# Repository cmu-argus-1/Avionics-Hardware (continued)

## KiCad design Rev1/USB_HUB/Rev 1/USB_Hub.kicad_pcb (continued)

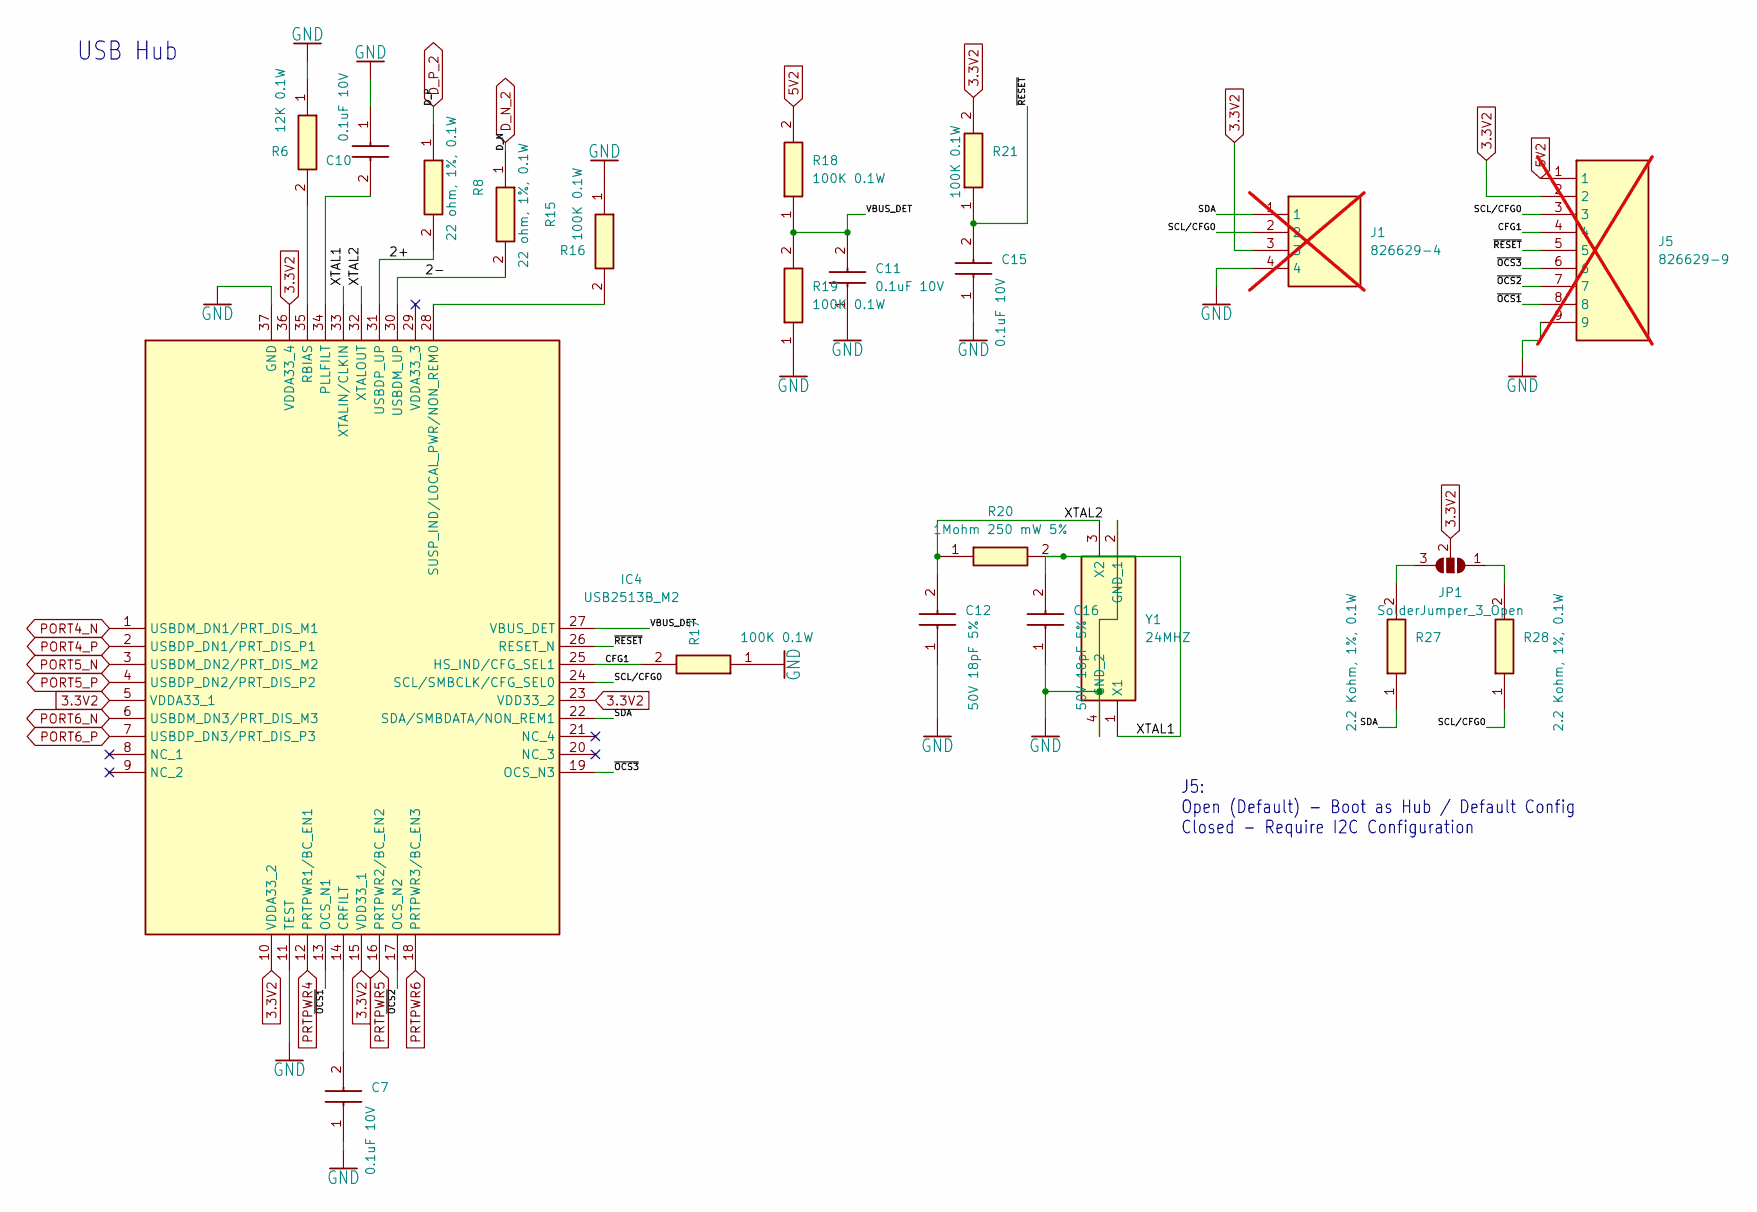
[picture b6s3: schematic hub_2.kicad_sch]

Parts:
C7, C10, C11, C15: 0.1uF 10V; CAPC1608X87N; Manufacturer_Part_Number C0603T104K8RAC7867; Mouser Part Number 80-C0603T104K8RACTU
C12, C16: 50V 18pF 5%; CAPC1608X90N; Manufacturer_Part_Number 06035A180J4T2A; Mouser Part Number 581-06035A180J4T2A
IC4: USB2513B_M2; QFN50P600X600X100-37N-D; Manufacturer_Part_Number USB2513B/M2; Mouser Part Number 579-USB2513B/M2
J1: 826629-4; HDRV4W63P0X254_1X4_1016X250X950P; Manufacturer_Part_Number 826629-4; Mouser Part Number 571-826629-4; not fitted
J5: 826629-9; HDRV9W63P0X254_1X9_2286X250X950P; Manufacturer_Part_Number 826629-9; Mouser Part Number 571-826629-9; not fitted
JP1: SolderJumper_3_Open; SolderJumper-3_P1.3mm_Open_Pad1.0x1.5mm_NumberLabels
R6: 12K 0.1W; RESC1608X55N; Manufacturer_Part_Number RMCF0603FT12K0
R8, R15: 22 ohm, 1%, 0.1W; RESC1608X55N; Manufacturer_Part_Number RMCF0603FT22R0
R16, R17, R18, R19, R21: 100K 0.1W; RESC1608X55N; Manufacturer_Part_Number RMCF0603FT100K; Mouser Part Number 708-RMCF0603FT100K
R20: 1Mohm 250 mW 5%; ERJP03_PA3__0603_; Manufacturer_Part_Number ERJ-PA3J105V; Mouser Part Number 667-ERJ-PA3J105V
R27, R28: 2.2 Kohm, 1%, 0.1W; RESC1608X55N; Manufacturer_Part_Number RMCF0603FT2K20
Y1: 24MHZ; ABM10W240000MHZ8K1ZT3; Manufacturer_Part_Number ABM10W-24.0000MHZ-7-B1U-T3

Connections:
3.3V2: IC4.5 (VDDA33_1), IC4.10 (VDDA33_2), IC4.15 (VDD33_1), IC4.23 (VDD33_2), IC4.36 (VDDA33_4), J1.3, J5.2, JP1.2 (C), R21.2; also elsewhere on the board
5V2: J5.1, R18.2; also elsewhere on the board
/hub_2/2+: IC4.31 (USBDP_UP), R8.2
/hub_2/2-: IC4.30 (USBDM_UP), R15.2
/hub_2/CFG1: IC4.25 (HS_IND/CFG_SEL1), J5.4, R17.2
/hub_2/SCL/CFG0: IC4.24 (SCL/SMBCLK/CFG_SEL0), J1.2, J5.3, R28.1
/hub_2/SDA: IC4.22 (SDA/SMBDATA/NON_REM1), J1.1, R27.1
/hub_2/VBUS_DET: C11.2, IC4.27 (VBUS_DET), R18.1, R19.2
/hub_2/XTAL1: C16.2, IC4.33 (XTALIN/CLKIN), R20.2, Y1.1 (X1)
/hub_2/XTAL2: C12.2, IC4.32 (XTALOUT), R20.1, Y1.3 (X2)
/hub_2/~OCS1: IC4.13 (OCS_N1), J5.8
/hub_2/~OCS2: IC4.17 (OCS_N2), J5.7
/hub_2/~OCS3: IC4.19 (OCS_N3), J5.6
/hub_2/~RESET: C15.2, IC4.26 (RESET_N), J5.5, R21.1
D_N_2: R15.1; also elsewhere on the board
D_P_2: R8.1; also elsewhere on the board
GND: C7.1, C10.1, C11.1, C12.1, C15.1, C16.1, IC4.11 (TEST), IC4.37 (GND), J1.4, J5.9, R6.1, R16.1, R17.1, R19.1, Y1.2 (GND_1), Y1.4 (GND_2); also elsewhere on the board
unnamed: C7.2, IC4.14 (CRFILT)
unnamed: C10.2, IC4.34 (PLLFILT)
unnamed: IC4.35 (RBIAS), R6.2
unnamed: IC4.28 (SUSP_IND/LOCAL_PWR/NON_REM0), R16.2
unnamed: JP1.1 (A), R28.2
unnamed: JP1.3 (B), R27.2
PORT4_N: IC4.1 (USBDM_DN1/PRT_DIS_M1); also elsewhere on the board
PORT4_P: IC4.2 (USBDP_DN1/PRT_DIS_P1); also elsewhere on the board
PORT5_N: IC4.3 (USBDM_DN2/PRT_DIS_M2); also elsewhere on the board
PORT5_P: IC4.4 (USBDP_DN2/PRT_DIS_P2); also elsewhere on the board
PORT6_N: IC4.6 (USBDM_DN3/PRT_DIS_M3); also elsewhere on the board
PORT6_P: IC4.7 (USBDP_DN3/PRT_DIS_P3); also elsewhere on the board
PRTPWR4: IC4.12 (PRTPWR1/BC_EN1); also elsewhere on the board
PRTPWR5: IC4.16 (PRTPWR2/BC_EN2); also elsewhere on the board
PRTPWR6: IC4.18 (PRTPWR3/BC_EN3); also elsewhere on the board

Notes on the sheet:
J5: Open (Default) - Boot as Hub / Default Config Closed - Require I2C Configuration
USB Hub

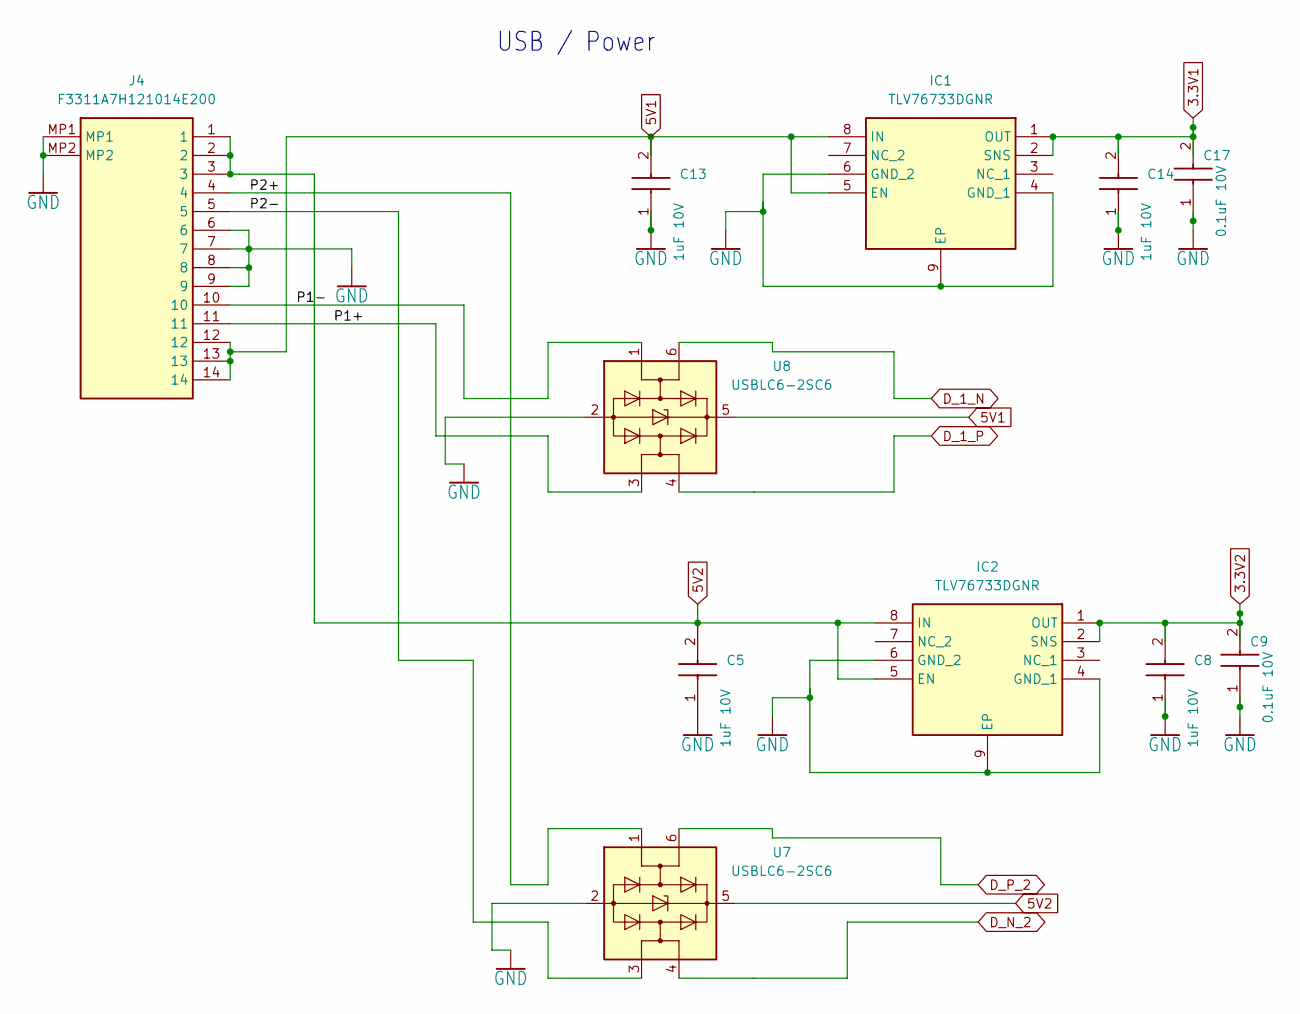
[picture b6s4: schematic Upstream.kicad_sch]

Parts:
C5, C8, C13, C14: 1uF 10V; CAPC1608X95N; Manufacturer_Part_Number CL10B105KB8NQNC; Mouser Part Number 187-CL10B105KB8NQNC
C9, C17: 0.1uF 10V; CAPC1608X87N; Manufacturer_Part_Number C0603T104K8RAC7867; Mouser Part Number 80-C0603T104K8RACTU
IC1, IC2: TLV76733DGNR; SOP65P490X110-9N; Manufacturer_Part_Number TLV76733DGNR; Mouser Part Number 595-TLV76733DGNR
J4: F3311A7H121014E200; Manufacturer_Part_Number F3311A7H121014E200
U7, U8: USBLC6-2SC6; SOT-23-6

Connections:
3.3V1: C14.2, C17.2, IC1.1 (OUT), IC1.2 (SNS); also elsewhere on the board
3.3V2: C8.2, C9.2, IC2.1 (OUT), IC2.2 (SNS); also elsewhere on the board
5V1: C13.2, IC1.5 (EN), IC1.8 (IN), J4.12, J4.13, J4.14, U8.5 (VBUS); also elsewhere on the board
5V2: C5.2, IC2.5 (EN), IC2.8 (IN), J4.1, J4.2, J4.3, U7.5 (VBUS); also elsewhere on the board
/Upstream/P1+: J4.11, U8.3 (I/O2)
/Upstream/P1-: J4.10, U8.1 (I/O1)
/Upstream/P2+: J4.4, U7.1 (I/O1)
/Upstream/P2-: J4.5, U7.3 (I/O2)
D_1_N: U8.6 (I/O1); also elsewhere on the board
D_1_P: U8.4 (I/O2); also elsewhere on the board
D_N_2: U7.4 (I/O2); also elsewhere on the board
D_P_2: U7.6 (I/O1); also elsewhere on the board
GND: C5.1, C8.1, C9.1, C13.1, C14.1, C17.1, IC1.4 (GND_1), IC1.6 (GND_2), IC1.9 (EP), IC2.4 (GND_1), IC2.6 (GND_2), IC2.9 (EP), J4.6, J4.7, J4.8, J4.9, J4.MP1, J4.MP2, U7.2 (GND), U8.2 (GND); also elsewhere on the board

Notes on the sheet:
USB / Power

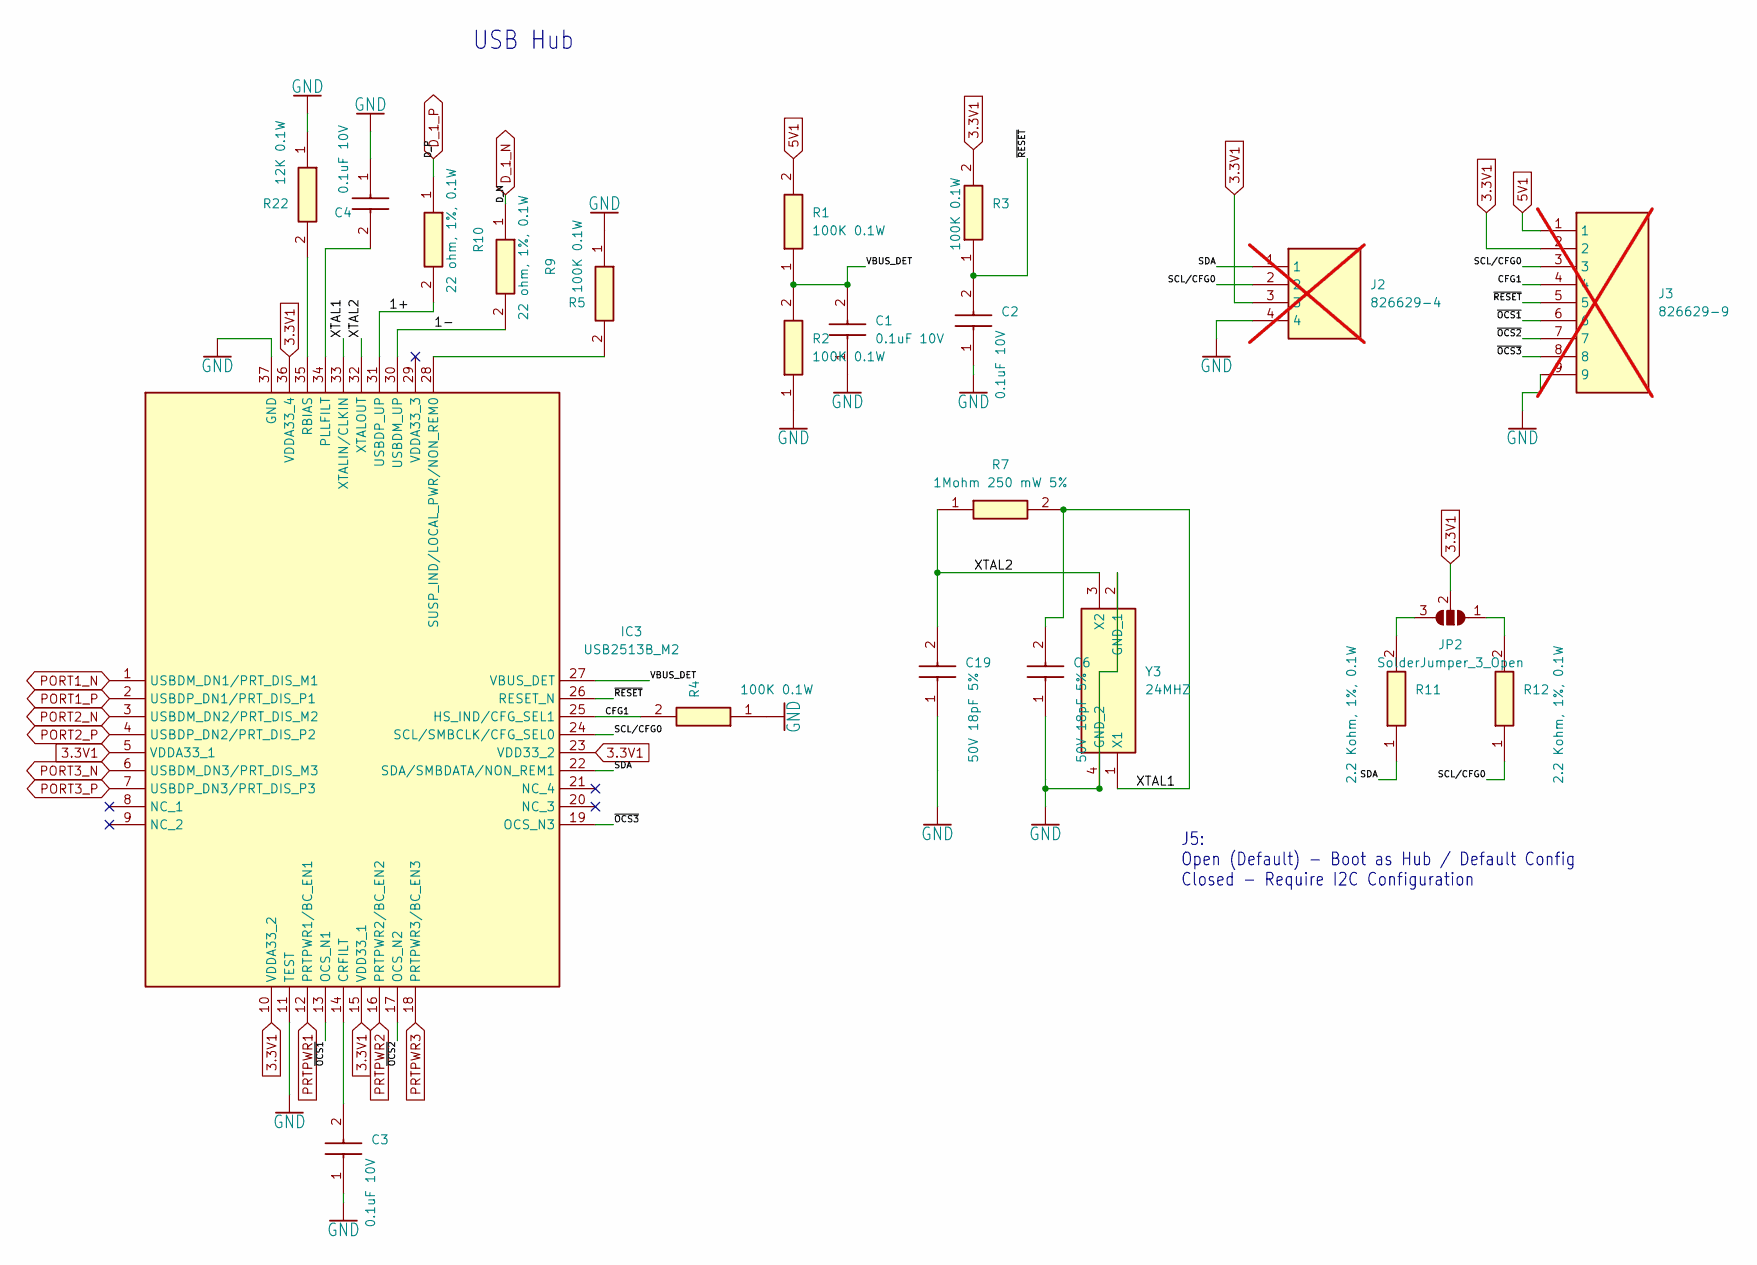
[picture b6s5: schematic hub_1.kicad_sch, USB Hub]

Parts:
C1, C2, C3, C4: 0.1uF 10V; CAPC1608X87N; Manufacturer_Part_Number C0603T104K8RAC7867; Mouser Part Number 80-C0603T104K8RACTU
C6, C19: 50V 18pF 5%; CAPC1608X90N; Manufacturer_Part_Number 06035A180J4T2A; Mouser Part Number 581-06035A180J4T2A
IC3: USB2513B_M2; QFN50P600X600X100-37N-D; Manufacturer_Part_Number USB2513B/M2; Mouser Part Number 579-USB2513B/M2
J2: 826629-4; HDRV4W63P0X254_1X4_1016X250X950P; Manufacturer_Part_Number 826629-4; Mouser Part Number 571-826629-4; not fitted
J3: 826629-9; HDRV9W63P0X254_1X9_2286X250X950P; Manufacturer_Part_Number 826629-9; Mouser Part Number 571-826629-9; not fitted
JP2: SolderJumper_3_Open; SolderJumper-3_P1.3mm_Open_Pad1.0x1.5mm_NumberLabels
R1, R2, R3, R4, R5: 100K 0.1W; RESC1608X55N; Manufacturer_Part_Number RMCF0603FT100K; Mouser Part Number 708-RMCF0603FT100K
R7: 1Mohm 250 mW 5%; ERJP03_PA3__0603_; Manufacturer_Part_Number ERJ-PA3J105V; Mouser Part Number 667-ERJ-PA3J105V
R9, R10: 22 ohm, 1%, 0.1W; RESC1608X55N; Manufacturer_Part_Number RMCF0603FT22R0
R11, R12: 2.2 Kohm, 1%, 0.1W; RESC1608X55N; Manufacturer_Part_Number RMCF0603FT2K20
R22: 12K 0.1W; RESC1608X55N; Manufacturer_Part_Number RMCF0603FT12K0
Y3: 24MHZ; ABM10W240000MHZ8K1ZT3; Manufacturer_Part_Number ABM10W-24.0000MHZ-7-B1U-T3

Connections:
3.3V1: IC3.5 (VDDA33_1), IC3.10 (VDDA33_2), IC3.15 (VDD33_1), IC3.23 (VDD33_2), IC3.36 (VDDA33_4), J2.3, J3.2, JP2.2 (C), R3.2; also elsewhere on the board
5V1: J3.1, R1.2; also elsewhere on the board
/hub_1/1+: IC3.31 (USBDP_UP), R10.2
/hub_1/1-: IC3.30 (USBDM_UP), R9.2
/hub_1/CFG1: IC3.25 (HS_IND/CFG_SEL1), J3.4, R4.2
/hub_1/SCL/CFG0: IC3.24 (SCL/SMBCLK/CFG_SEL0), J2.2, J3.3, R12.1
/hub_1/SDA: IC3.22 (SDA/SMBDATA/NON_REM1), J2.1, R11.1
/hub_1/VBUS_DET: C1.2, IC3.27 (VBUS_DET), R1.1, R2.2
/hub_1/XTAL1: C6.2, IC3.33 (XTALIN/CLKIN), R7.2, Y3.1 (X1)
/hub_1/XTAL2: C19.2, IC3.32 (XTALOUT), R7.1, Y3.3 (X2)
/hub_1/~OCS1: IC3.13 (OCS_N1), J3.6
/hub_1/~OCS2: IC3.17 (OCS_N2), J3.7
/hub_1/~OCS3: IC3.19 (OCS_N3), J3.8
/hub_1/~RESET: C2.2, IC3.26 (RESET_N), J3.5, R3.1
D_1_N: R9.1; also elsewhere on the board
D_1_P: R10.1; also elsewhere on the board
GND: C1.1, C2.1, C3.1, C4.1, C6.1, C19.1, IC3.11 (TEST), IC3.37 (GND), J2.4, J3.9, R2.1, R4.1, R5.1, R22.1, Y3.2 (GND_1), Y3.4 (GND_2); also elsewhere on the board
unnamed: C3.2, IC3.14 (CRFILT)
unnamed: C4.2, IC3.34 (PLLFILT)
unnamed: IC3.35 (RBIAS), R22.2
unnamed: IC3.28 (SUSP_IND/LOCAL_PWR/NON_REM0), R5.2
unnamed: JP2.1 (A), R12.2
unnamed: JP2.3 (B), R11.2
PORT1_N: IC3.1 (USBDM_DN1/PRT_DIS_M1); also elsewhere on the board
PORT1_P: IC3.2 (USBDP_DN1/PRT_DIS_P1); also elsewhere on the board
PORT2_N: IC3.3 (USBDM_DN2/PRT_DIS_M2); also elsewhere on the board
PORT2_P: IC3.4 (USBDP_DN2/PRT_DIS_P2); also elsewhere on the board
PORT3_N: IC3.6 (USBDM_DN3/PRT_DIS_M3); also elsewhere on the board
PORT3_P: IC3.7 (USBDP_DN3/PRT_DIS_P3); also elsewhere on the board
PRTPWR1: IC3.12 (PRTPWR1/BC_EN1); also elsewhere on the board
PRTPWR2: IC3.16 (PRTPWR2/BC_EN2); also elsewhere on the board
PRTPWR3: IC3.18 (PRTPWR3/BC_EN3); also elsewhere on the board

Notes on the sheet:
USB Hub
J5: Open (Default) - Boot as Hub / Default Config Closed - Require I2C Configuration

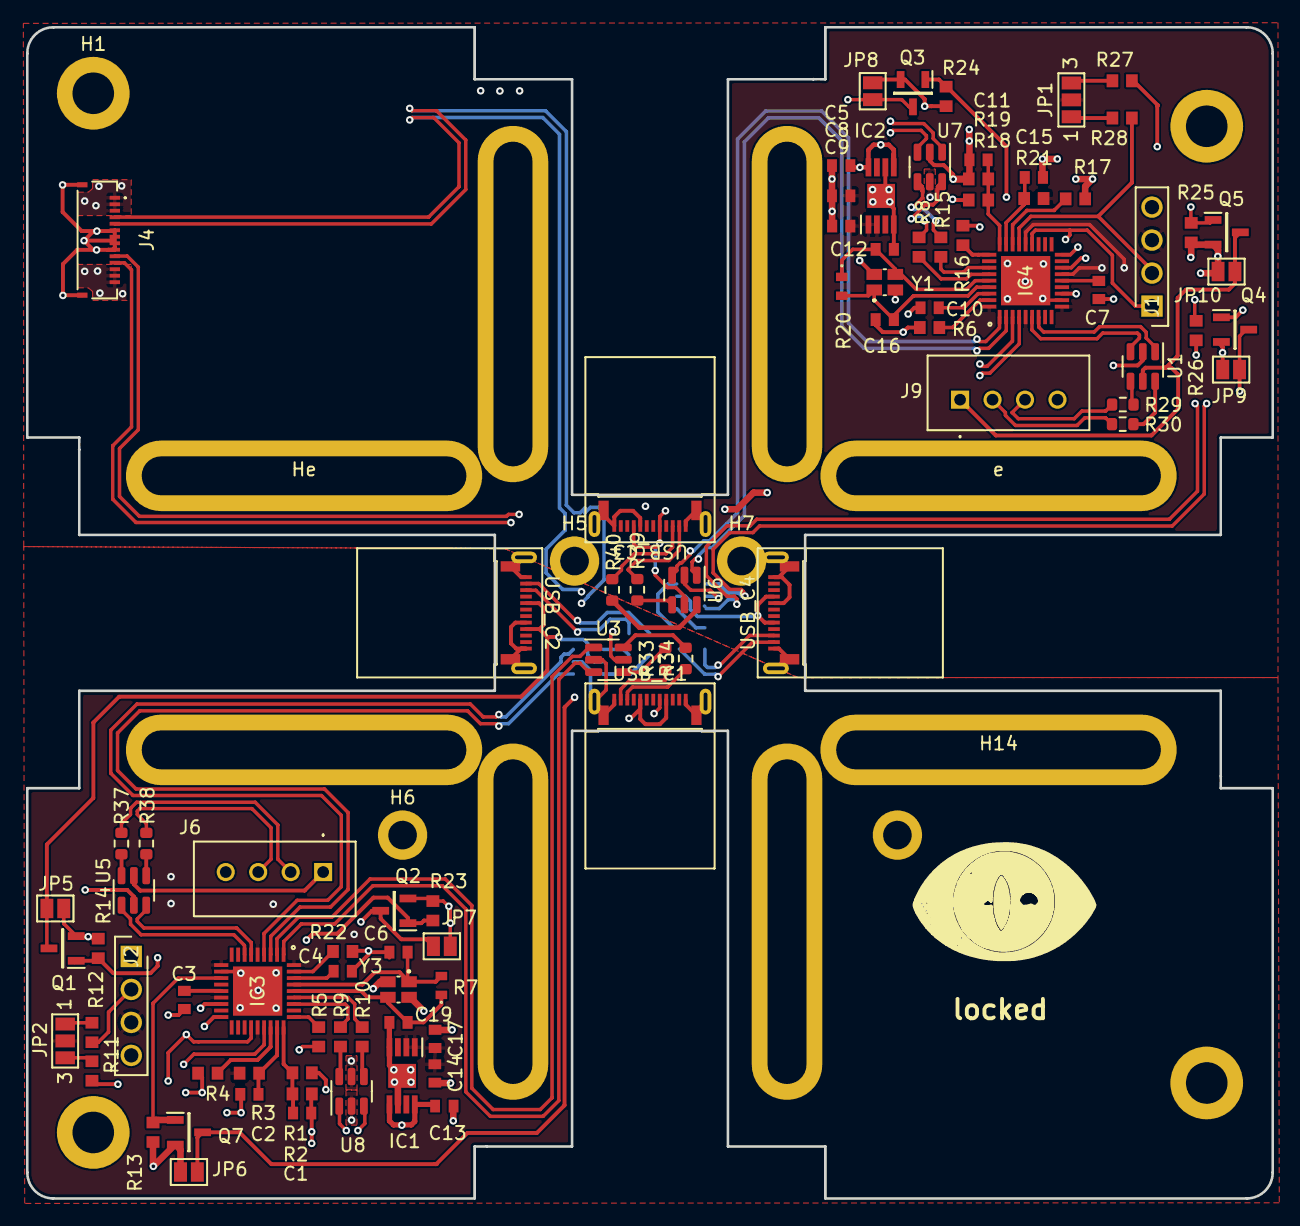
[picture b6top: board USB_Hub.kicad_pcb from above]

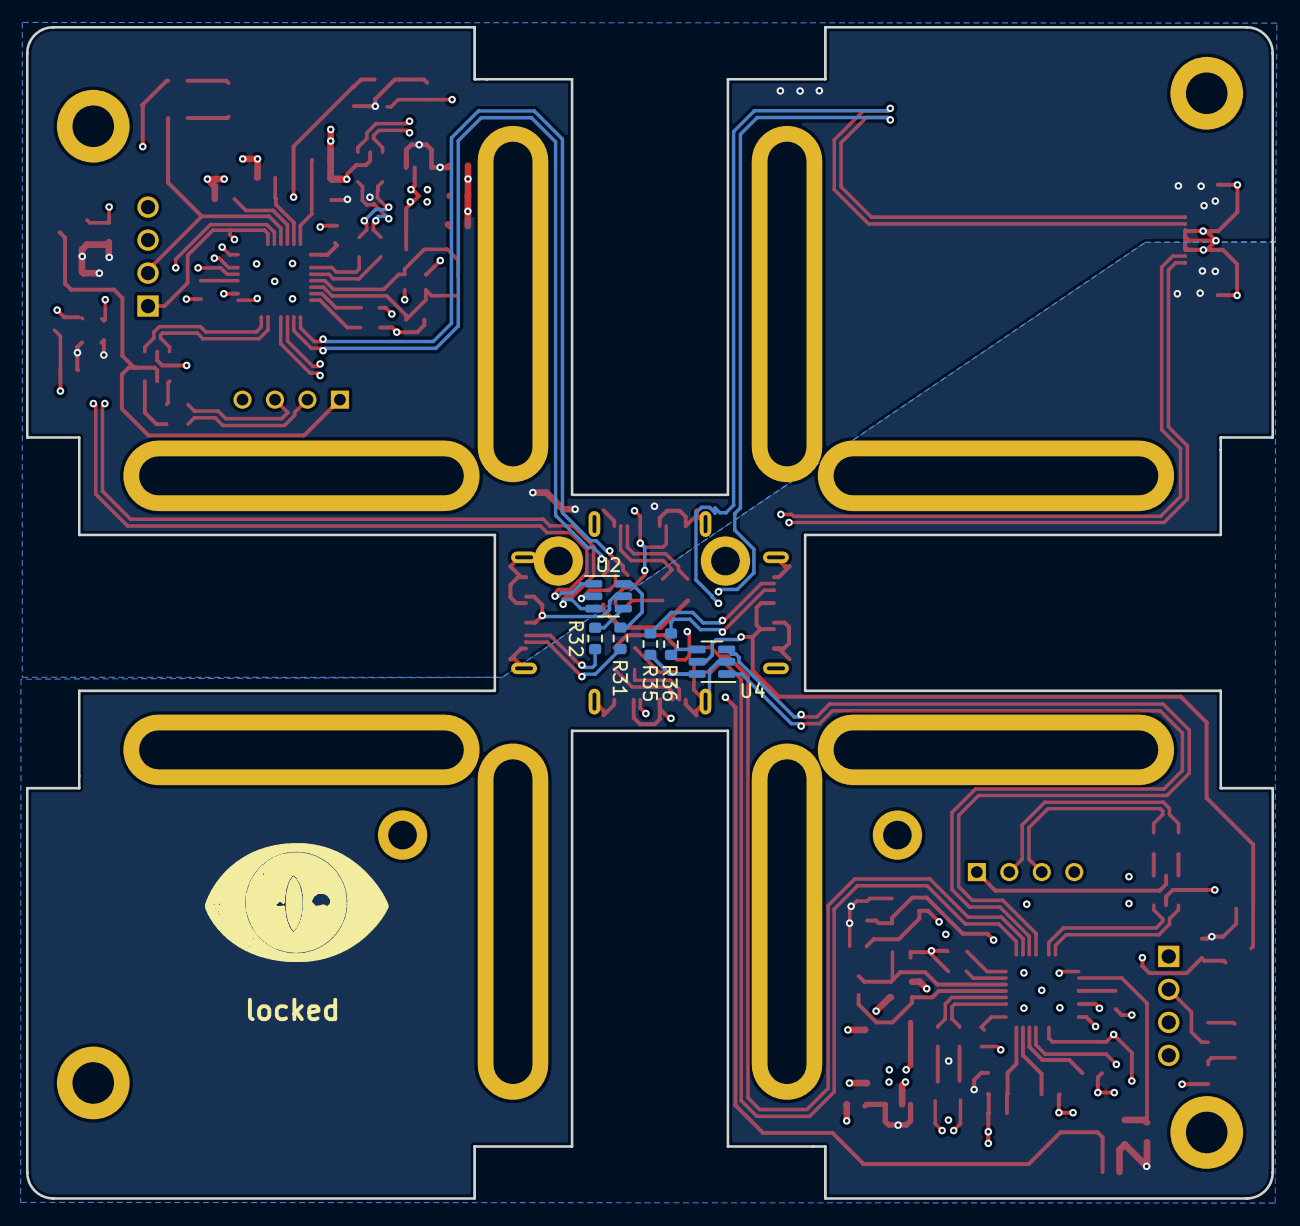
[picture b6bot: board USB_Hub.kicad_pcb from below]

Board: 4 copper layers, 95.9 x 90.2 mm, 111 parts (6 on the bottom side), 91 nets.

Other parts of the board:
He: MountingHole_Pad; MountingHole_USB
e: MountingHole_Pad; MountingHole_USB

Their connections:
GND: He.1, e.1; also elsewhere on the board

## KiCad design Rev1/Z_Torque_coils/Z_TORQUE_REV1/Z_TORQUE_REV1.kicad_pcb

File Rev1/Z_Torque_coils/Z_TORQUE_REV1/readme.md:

# Check off list
## Please check the box add your name and time.
## add "[x]" for checking off a list item, please make sure you edit the readme file and then commit and push or else the change wont take place.
- [x] Avionics Signoff made by Nischal 
- [] Mechanical Signoff made by  at time and 
- [x] TA signoff by __ at time __ and date __
- [ ] Board list sent by -- to -- at time __ and date __
- [ ] Parts list by -- to -- at time __ and date __
- [ ] Board ordered by -- at time __ and date __
- [ ] Parts Ordered by -- at time __ and date __
- [ ] Board received -- at time __ and date __
- [ ] Parts Received  at time __ and date __
- [ ] Boards Built at time __ and date __
- [ ] Boards tested at time __ and date __
- [ ] Boards ready at time __ and date __

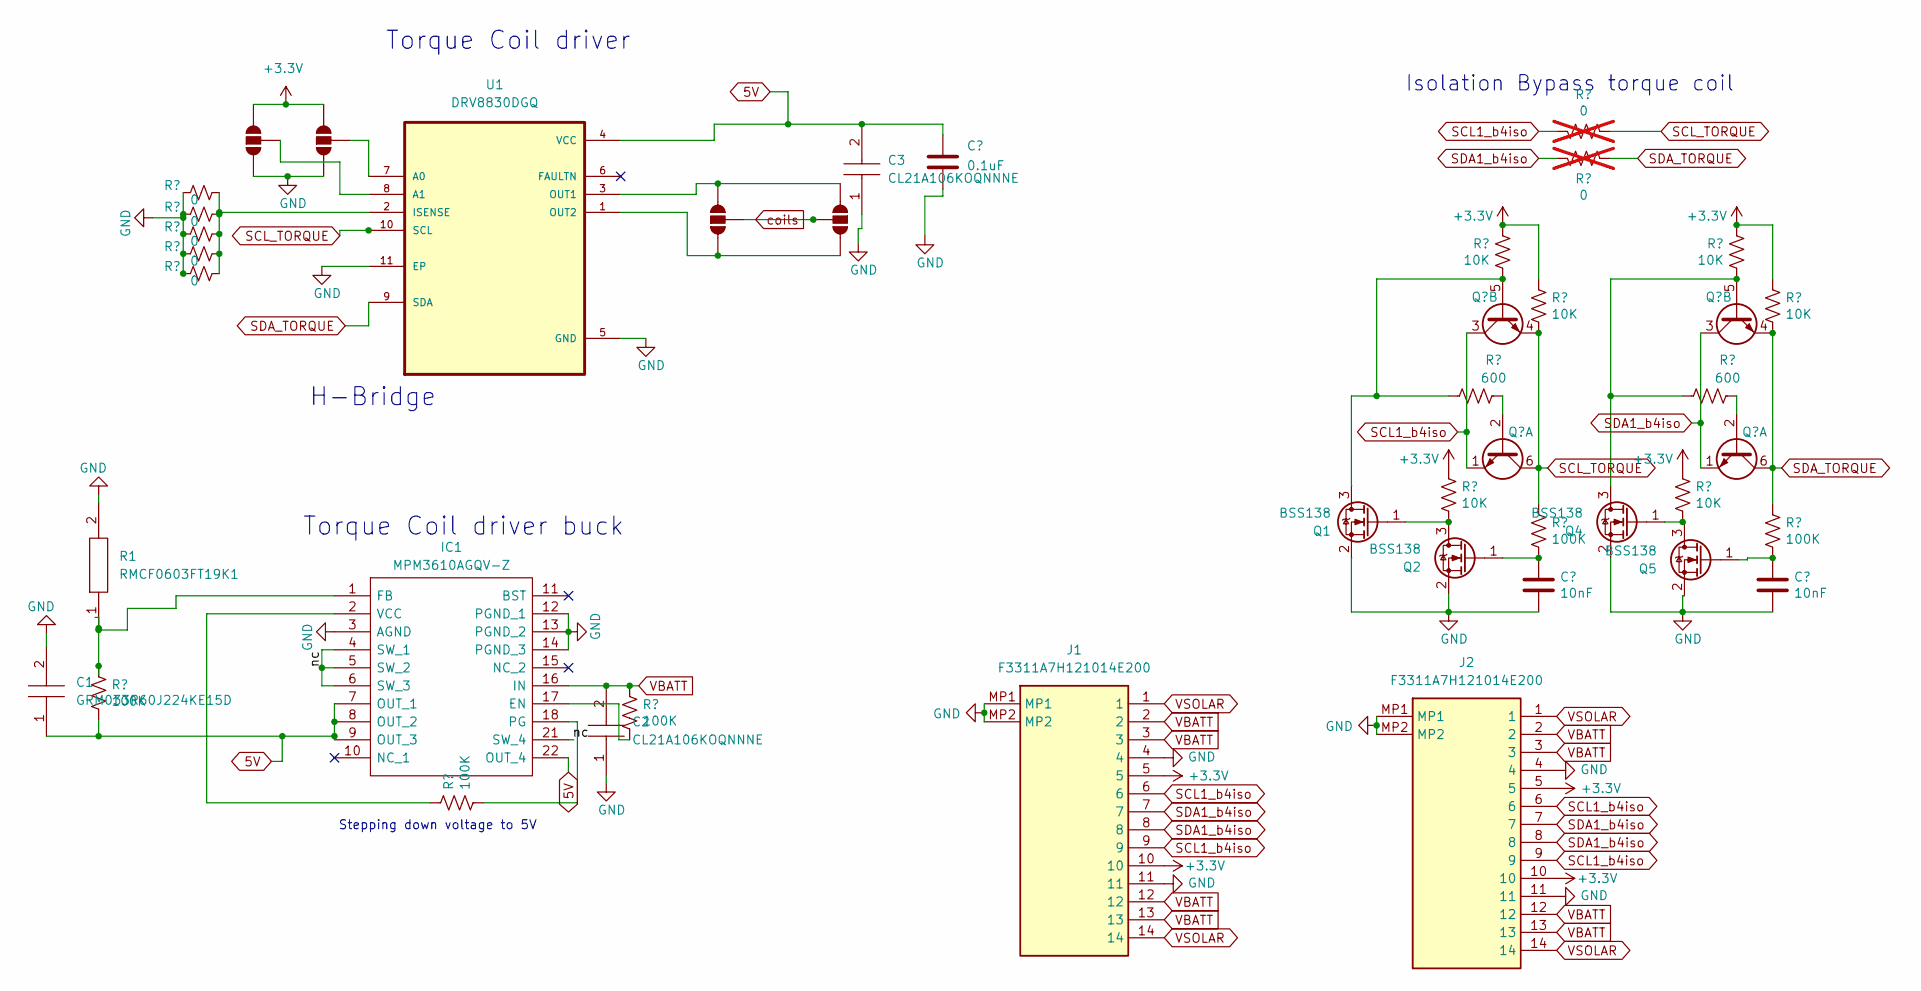
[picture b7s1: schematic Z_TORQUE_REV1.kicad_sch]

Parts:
C1: GRM033R60J224KE15D; CAPC0603X33N; Manufacturer_Part_Number GRM033R60J224KE15D; Mouser Part Number 81-GRM33R60J224KE15D
C2, C3: CL21A106KOQNNNE; CAPC2012X140N; Manufacturer_Part_Number CL21A106KOQNNNE; Mouser Part Number 187-CL21A106KOQNNNE
C4: 0.1uF; C_0805_2012Metric
C5, C6: 10nF; C_0201_0603Metric
IC1: MPM3610AGQV-Z; MPM3610AGQVZ; Manufacturer_Part_Number MPM3610AGQV-Z; Mouser Part Number 946-MPM3610AGQV-Z
J1, J2: F3311A7H121014E200; Manufacturer_Part_Number F3311A7H121014E200
JP1, JP2, JP3, JP4: SMT-JUMPER_3_NO_NO-SILK
Q1, Q2, Q4, Q5: BSS138; SOT-23
Q3, Q6: MBT2222ADW1T1; SOT-363_SC-70-6
R1: RMCF0603FT19K1; RESC1608X55N; Manufacturer_Part_Number RMCF0603FT19K1
R2, R9: 100K; R_0805_2012Metric_Pad1.20x1.40mm_HandSolder
R3, R4, R5, R6, R7: 0; R_0805_2012Metric_Pad1.20x1.40mm_HandSolder
R8, R14, R21: 100K; R_0805_2012Metric
R10, R12, R13, R17, R19, R20: 10K; R_0805_2012Metric
R11, R18: 600; R_0805_2012Metric
R15, R16: 0; R_0603_1608Metric; not fitted
U1: DRV8830DGQ; IC_XTR111AIDGQR

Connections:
5V: C1.1, C3.2, C4.1, IC1.7 (OUT_1), IC1.8 (OUT_2), IC1.9 (OUT_3), IC1.22 (OUT_4), R2.1, U1.4 (VCC)
+3.3V: J1.5, J1.10, J2.5, J2.10, JP1.3 (B), JP2.3 (B), R10.2, R12.1, R13.2, R17.2, R19.1, R20.2
/nc: IC1.4 (SW_1), IC1.5 (SW_2), IC1.6 (SW_3), IC1.21 (SW_4)
GND: C1.2, C2.1, C3.1, C4.2, C5.2, C6.2, IC1.3 (AGND), IC1.12 (PGND_1), IC1.13 (PGND_2), IC1.14 (PGND_3), J1.4, J1.11, J1.MP1, J1.MP2, J2.4, J2.11, J2.MP1, J2.MP2, JP1.1 (A), JP2.1 (A), Q1.2 (S), Q2.2 (S), Q4.2 (S), Q5.2 (S), R1.2, R3.2, R4.2, R5.2, R6.2, R7.2, U1.5 (GND), U1.11 (EP)
unnamed: IC1.17 (EN), R9.1
unnamed: IC1.1 (FB), R1.1, R2.2
unnamed: IC1.18 (PG), R8.1
unnamed: IC1.2 (VCC), R8.2
unnamed: JP1.2 (C), U1.8 (A1)
unnamed: JP2.2 (C), U1.7 (A0)
unnamed: JP3.1 (A), JP4.3 (B), U1.1 (OUT2)
unnamed: JP3.3 (B), JP4.1 (A), U1.3 (OUT1)
unnamed: Q1.3 (D), Q3.5 (B2), R11.1, R12.2
unnamed: Q1.1 (G), Q2.3 (D), R10.1
unnamed: C5.1, Q2.1 (G), R14.1
unnamed: Q3.2 (B1), R11.2
unnamed: Q4.3 (D), Q6.5 (B2), R18.2, R19.2
unnamed: Q4.1 (G), Q5.3 (D), R17.1
unnamed: C6.1, Q5.1 (G), R21.1
unnamed: Q6.2 (B1), R18.1
unnamed: R3.1, R4.1, R5.1, R6.1, R7.1, U1.2 (ISENSE)
SCL1_b4iso: J1.6, J1.9, J2.6, J2.9, Q3.1 (E1), Q3.3 (C2), R15.1
SCL_TORQUE: Q3.4 (E2), Q3.6 (C1), R13.1, R14.2, R15.2, U1.10 (SCL)
SDA1_b4iso: J1.7, J1.8, J2.7, J2.8, Q6.1 (E1), Q6.3 (C2), R16.1
SDA_TORQUE: Q6.4 (E2), Q6.6 (C1), R16.2, R20.1, R21.2, U1.9 (SDA)
VBATT: C2.2, IC1.16 (IN), J1.2, J1.3, J1.12, J1.13, J2.2, J2.3, J2.12, J2.13, R9.2
VSOLAR: J1.1, J1.14, J2.1, J2.14
coils: JP3.2 (C), JP4.2 (C)

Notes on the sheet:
Torque Coil driver buck
Stepping down voltage to 5V
Torque Coil driver
Isolation Bypass torque coil
H-Bridge

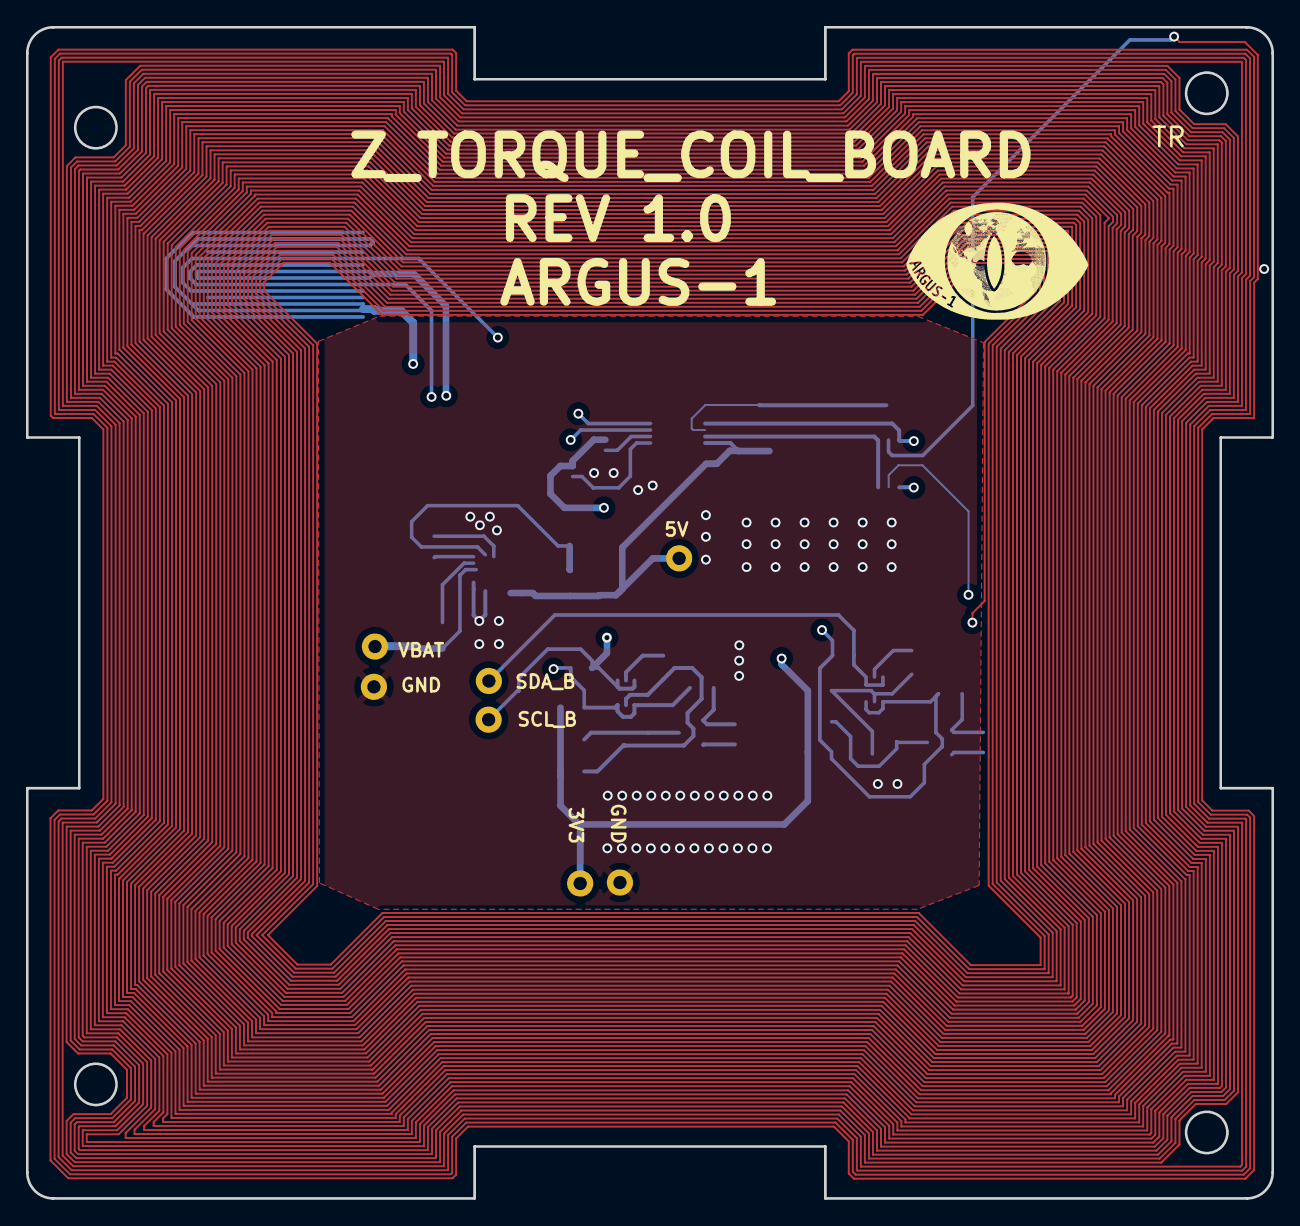
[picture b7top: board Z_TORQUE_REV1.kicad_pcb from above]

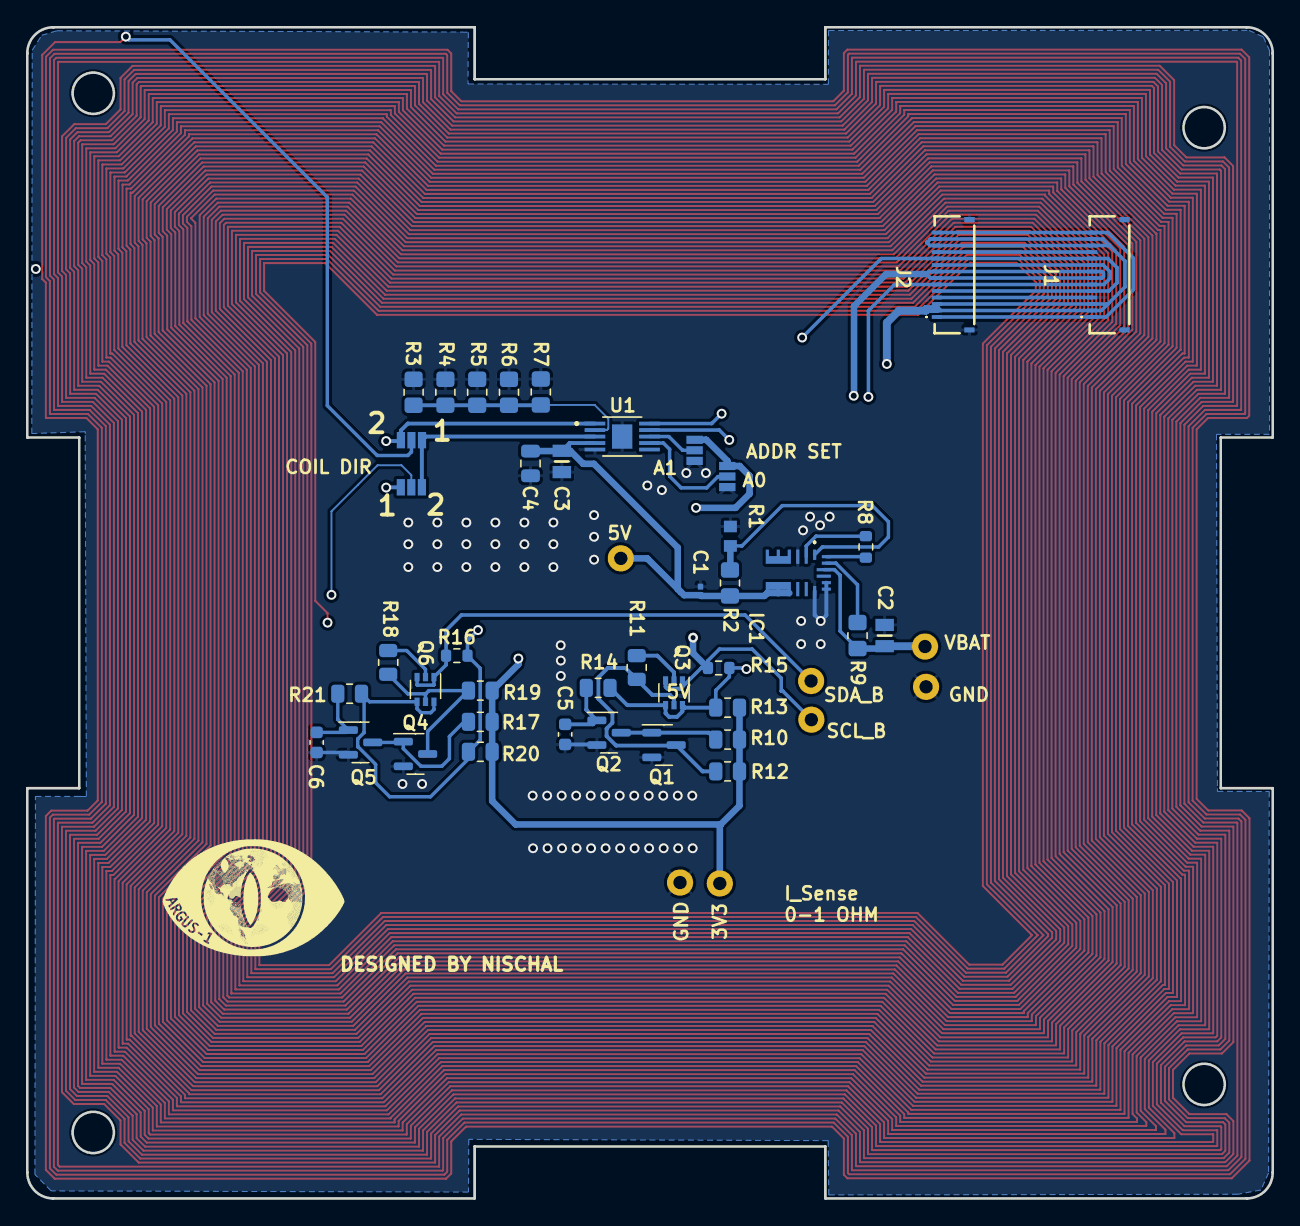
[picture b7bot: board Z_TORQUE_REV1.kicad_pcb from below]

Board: 4 copper layers, 95.9 x 90.2 mm, 43 parts (42 on the bottom side), 28 nets.

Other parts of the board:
., .#2: .; Argus LOGO
